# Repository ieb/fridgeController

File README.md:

#  Fridge Controller

This is a controller for 12V Danfoss and Secomp fridges. The compressors on these fridges are
variable speed and typically have switch based external temperature sensors. In a low power
environment running off 12v there are a few problems, which can be addressed by buying one
of the top end control heads. Some of documentation for the newer compressors indicate that
the RPM and minimum battery voltages have more control, but the BD35 and BD50 compressors
while being variable speed have unsuitable battery shutoff voltages.

# Why ?

I've gone through 2x 300 Lead Acid battery sets due to the behavior of the Fridge Compressor, in the past 6 years. Perhaps 3 years is ok for flooded or AGM, but there have been perhaps 60 charge cycles per year, so 180 in total and the batteries have always been kept fully charged. Could be bad luck buying batteries claiming not to be what they are.... but they were not the cheapest and weighed almost the same as Rolls equivalents. (ie same volume of lead).

# Fridge hardware

The compressor (BD35) is a variable speed motor that runs at between 2000 and 3500 RPM. In basic setups
the speed is controlled current from one of the pins on the control unit of between 2mA (3500rpm) and 5mA (2000rpm).
Typically manufacturers add a fixed resistor to achieve this, loosing the benefits of variable speed control,
which allow these compressors to use significantly less energy than the fixed speed counterparts.

The controllers have a battery low voltage cutout which is set by another resistor. Typically this defaults to 10.7v but
can be lowered to 9.6v for solar only applications or 11.7v for other applications. All these voltages are sufficiently
low enough to damage most lead acid batteries, and certainly well below the manufacturer recommended minimum discharge
level of 12.2v. The saving grace is that many fridge cables will be long and there might be enough voltage drop to
disable the fridge before the damage is done (repeatedly). Second saving grace is after the damage is done the battery is
unlikely to maintain is voltage while the fridge is on and should drop to below these levels, switching the fridge off and
then recovering. Typically this is accompanied with low voltage alarms on other systems supplied by the same battery.

The control units for the compressor have a electronic CCU built in. It has a LIN interface (19200 baud 8-n-1 serial),
with the same electrical characteristics found on many K-LINE car interfaces in cars. Cheap pass-through K-LINE OBDII
adapters will almost certainly work. The protocol is similar to Modbus and allows access to almost all parameters, 
however the documentation on the format of the parameters is very sparse. There is a free windows utility xtool4cool, from
secop that allows access to the parameters, but, TBH, this interface is intended for manufacturing and is not worth the
effort to reverse engineer (imho).

The restive compressor control mentioned above can also be controlled by a 5KHz PWM signal driving an open collector NPN
transistor, the collector connected to the control pin. There are no specifications available on the duty cycle but I 
am going to assume the aim is to sink between 2mA and 5mA.

# This hardware

I thought about a Attiny3224, Atmega328p (Pro Mini) or ESP32, all are possible, but I dont want to have a screen as it 
draws too much power and needs buttons, and cant be hidden. Setup will be over serial. Attiny3224 and Atmega328p need a
serial adapter which is why the ESP32 is being chosen. If I want to run BLE then it will be enabled with a push button. 
Current draw on previous projects has been around 30mA which is ok given the Fridge when on draws 7A. When not connected
the onboard LED on the ESP32 indicates state... and if you want to know if the fridge is on... the compressor makes a sound. 

Control is maintained with 3 states, 0, 1, 2. Charging, Normal, Low Battery. On and off temperatures and compressor rpm
can be set for each state as cant a minimum charging and battery voltage. If the device enters a Low Battery state it can 
transition into the charging state when the minimum charging voltage is exceeded.

Voltages are measured with the ESP32 ADC via a voltage divider that keeps the ADC voltage < 2.5v and so in its linear range. (> 2.5 ESP32s ADC becomes quite non linear). The PWM output uses the wonderfully simple ESP32 led control API. For atMega and atTiny versions see the secoppower.cpp files for those chips. (That code has never been run so expect bugs in it).

The compressor RPM can be varied depending on the difference between measured temperature and target temperature. Temperature is measured over 1wire sensors which are so slow, but fast enough for this use. 1Wire measurements are using asynchronous requests.

# Compressor control.

Fridge circuits work by compressing the refrigerant, cooling it into a liquid form in a condensor, storing the refrigerant liquid in a reservoir. The liquid escapes through a metering device which lowers the pressure of the liquid. On entering the evaporator the liquid boils removing heat from the fridge. The gas returns to the compressor which re-compresses the gas back into a liquid.  Marine fridges tend to use a long capillary tube as the metering device, which is static. The reservwoir is generally quite small. Because the metering is fixed, there is little point in running the compressor at full speed exit temperature of the evaporator is low enough to generate frost, ie < 0C as that will only cool the atomsphere. So a temperature sensor at the exit of the evaporator could be used to control the speed of the compressor to ensure that only enough energy to is put into the compressor to cool the evaporator and not the pipes outside the fridge.  

## Temperature sensor locations.

* Input side of the evaporator, probably central - this is the default location on standard installation.
* Output side if the evaporator - outside the fridge but as far a away from the compressor as possible.
* Interior of fridge.

## Control mechanism.

Control of RPM should be based on the relative temperatures of the evaporator at both ends. The on and off temperature of the fridge should depend on the battery state, with the fridge being off if the voltage falls too low.

# Building

use pio command line and upload.

# Configuring

The serial port runs at 115200 8N1, press h for a menu with options. The PWM duty cycle to rpm mapping will need to be calabrated.

# PCB

Very simple schematic, see files in pcb/

# TODO

- [ ] build pcb
- [ ] hookup and test
- [ ] make use of the variable speed compressor
- [ ] Enable BLE
- [ ] Write Android or Chromium app.

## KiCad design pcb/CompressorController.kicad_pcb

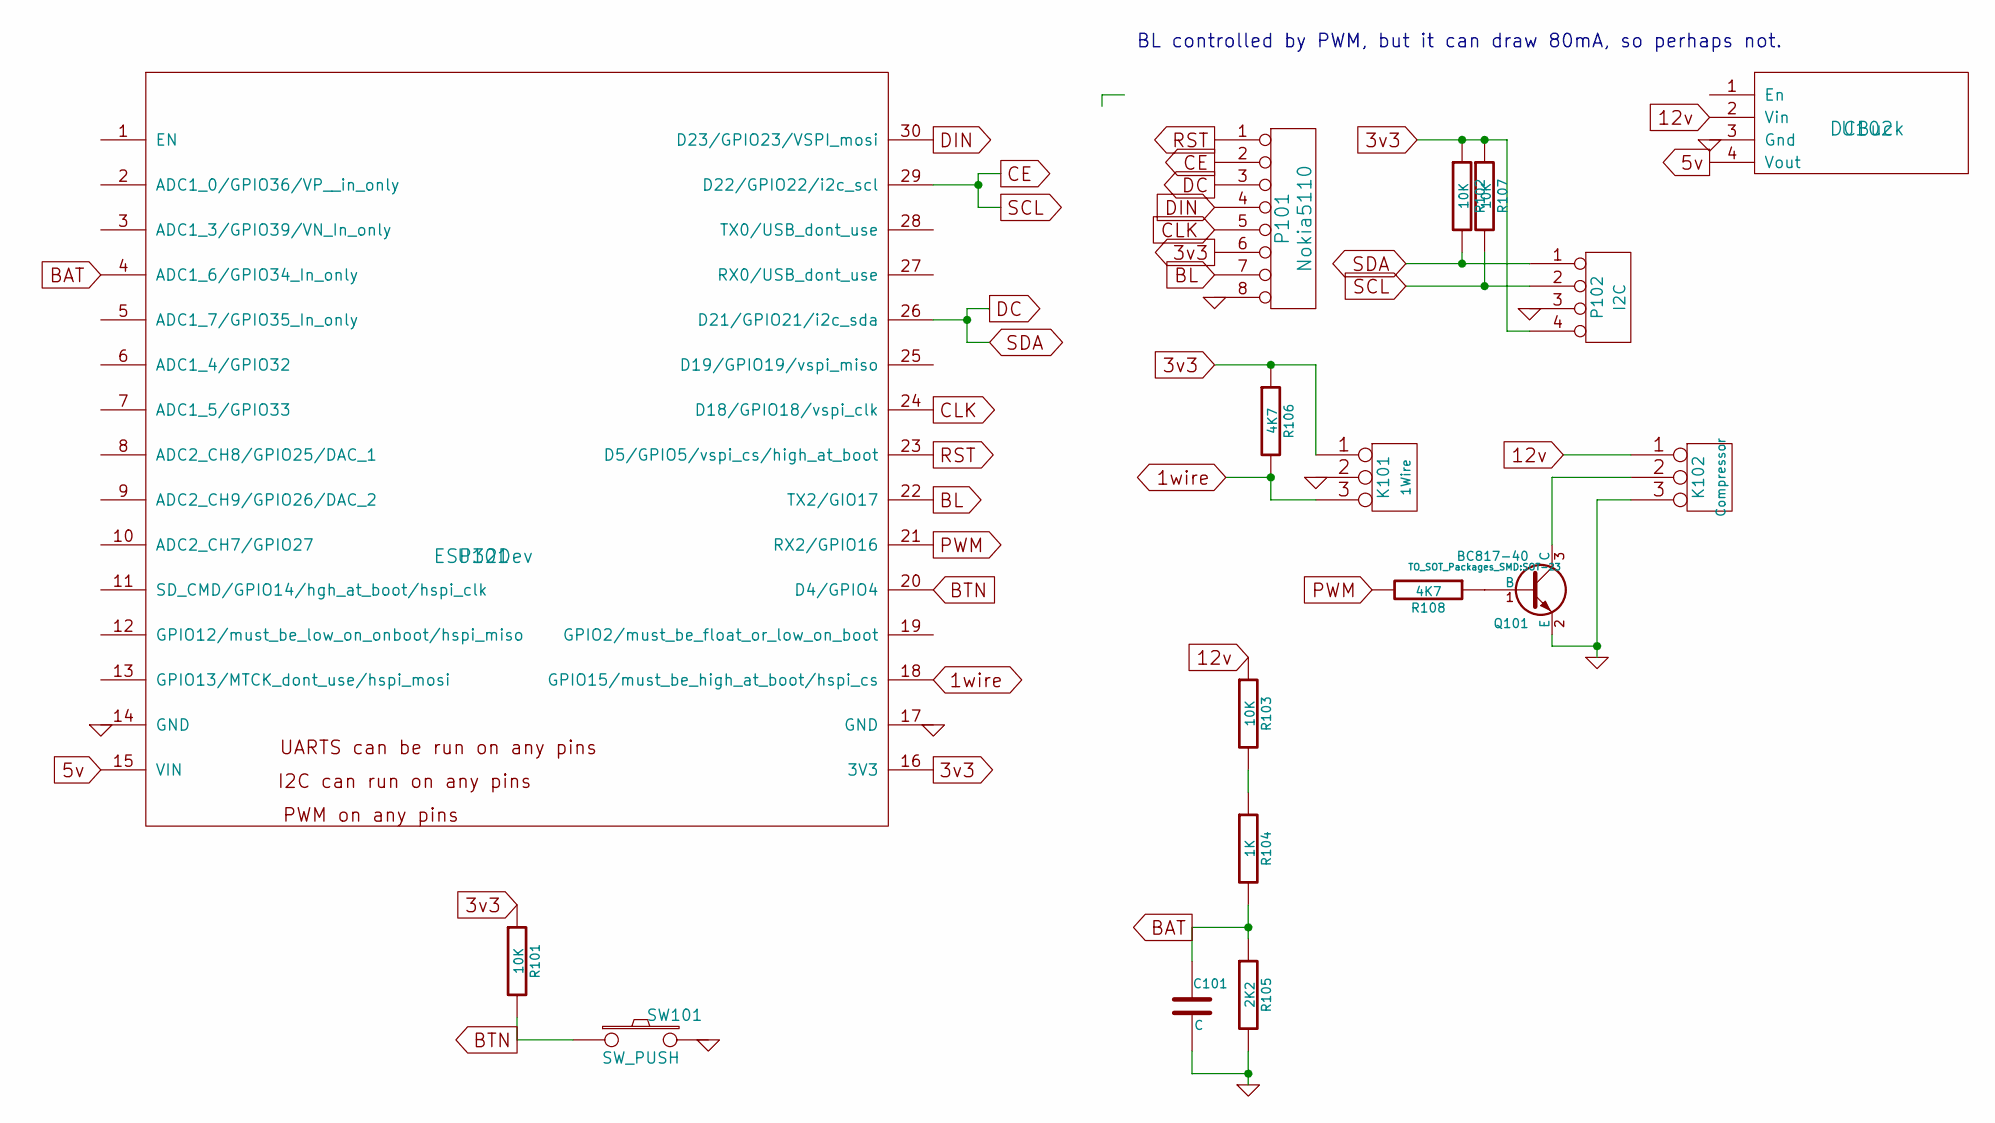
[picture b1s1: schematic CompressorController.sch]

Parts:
C101: C; C_0805_HandSoldering
K101: 1Wire; bornier3
K102: Compressor; bornier3
P101: Nokia5110; Pin_Header_Straight_1x08
P102: I2C; Pin_Header_Straight_1x04
Q101: BC817-40; SOT-23
R101, R102, R103, R107: 10K; R_0805_HandSoldering
R104: 1K; R_0805_HandSoldering
R105: 2K2; R_0805_HandSoldering
R106, R108: 4K7; R_0805_HandSoldering
SW101: SW_PUSH; SW_PUSH_6mm
U101: ESP32Dev
U102: DCBuck; DCBuckModule

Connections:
1wire: K101.3, R106.2, U101.18 (GPIO15/must_be_high_at_boot/hspi_cs)
3v3: K101.1, P101.6, P102.4, R101.1, R102.1, R106.1, R107.1, U101.16 (3V3)
5v: U101.15 (VIN), U102.4 (Vout)
12v: K102.1, R103.1, U102.2 (Vin)
BAT: C101.1, R104.2, R105.1, U101.4 (ADC1_6/GPIO34_In_only)
BL: P101.7, U101.22 (TX2/GIO17)
BTN: R101.2, SW101.1, U101.20 (D4/GPIO4)
CE: P101.2, P102.2, R107.2, U101.29 (D22/GPIO22/i2c_scl)
CLK: P101.5, U101.24 (D18/GPIO18/vspi_clk)
DC: P101.3, P102.1, R102.2, U101.26 (D21/GPIO21/i2c_sda)
DIN: P101.4, U101.30 (D23/GPIO23/VSPI_mosi)
GND: C101.2, K101.2 (PM), K102.3, P101.8, P102.3, Q101.2 (E), R105.2, SW101.2, U101.14 (GND), U101.17 (GND), U102.3 (Gnd)
unnamed: K102.2 (PM), Q101.3 (C)
unnamed: Q101.1 (B), R108.1
unnamed: R103.2, R104.1
PWM: R108.2, U101.21 (RX2/GPIO16)
RST: P101.1, U101.23 (D5/GPIO5/vspi_cs/high_at_boot)

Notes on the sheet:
BL controlled by PWM, but it can draw 80mA, so perhaps not.

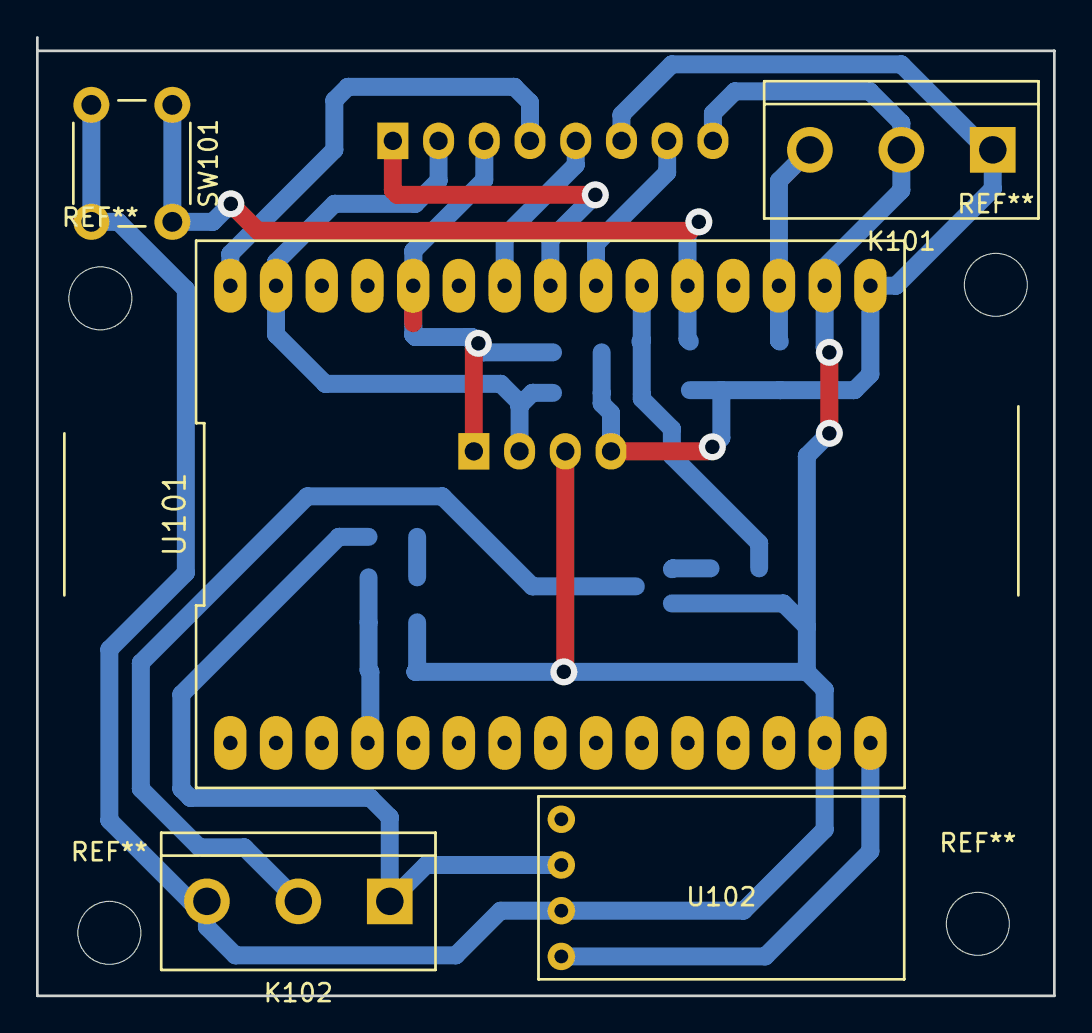
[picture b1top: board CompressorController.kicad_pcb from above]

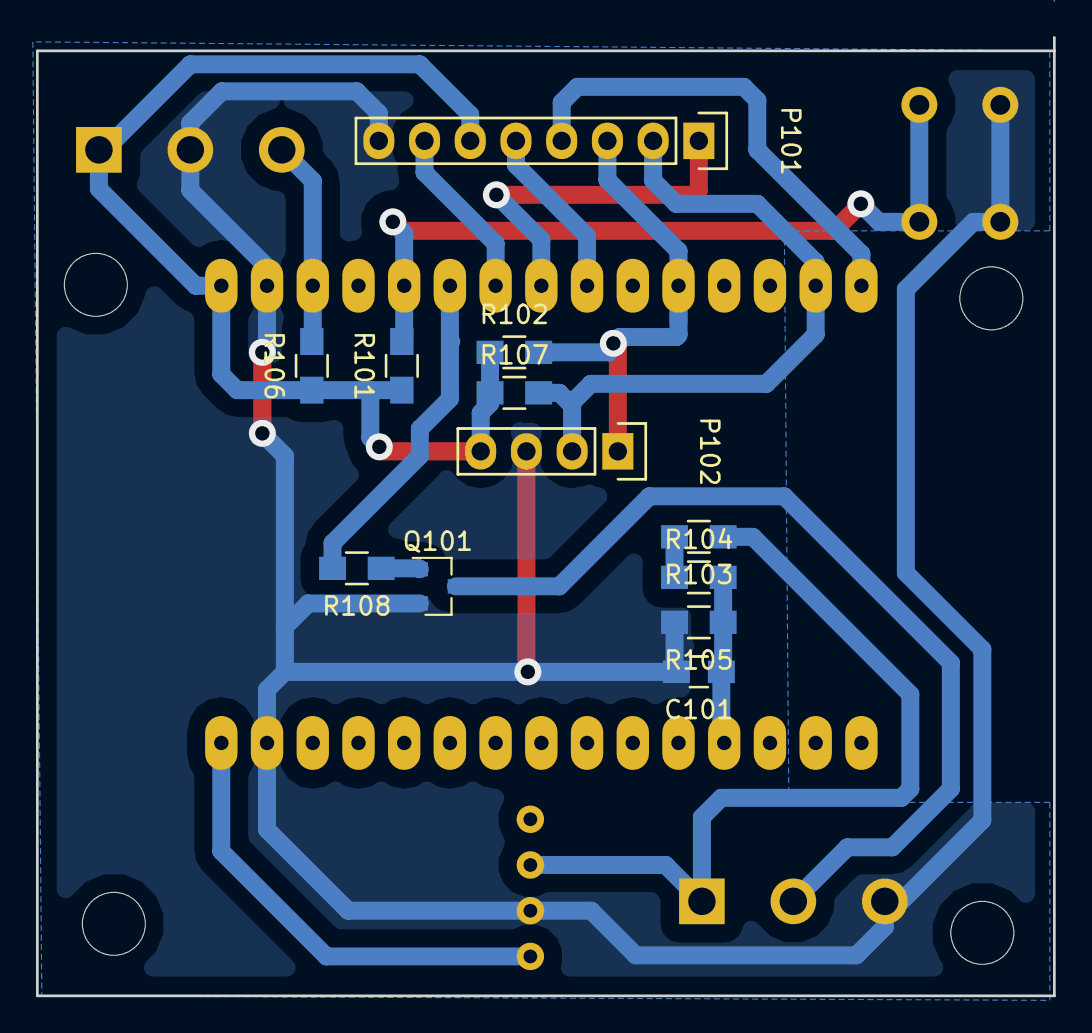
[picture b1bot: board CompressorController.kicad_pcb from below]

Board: 2 copper layers, 56.5 x 53.2 mm, 17 parts (12 on the bottom side), 17 nets.

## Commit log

2023-09-18 Added display
2023-09-20 Switched to using nvs for config
